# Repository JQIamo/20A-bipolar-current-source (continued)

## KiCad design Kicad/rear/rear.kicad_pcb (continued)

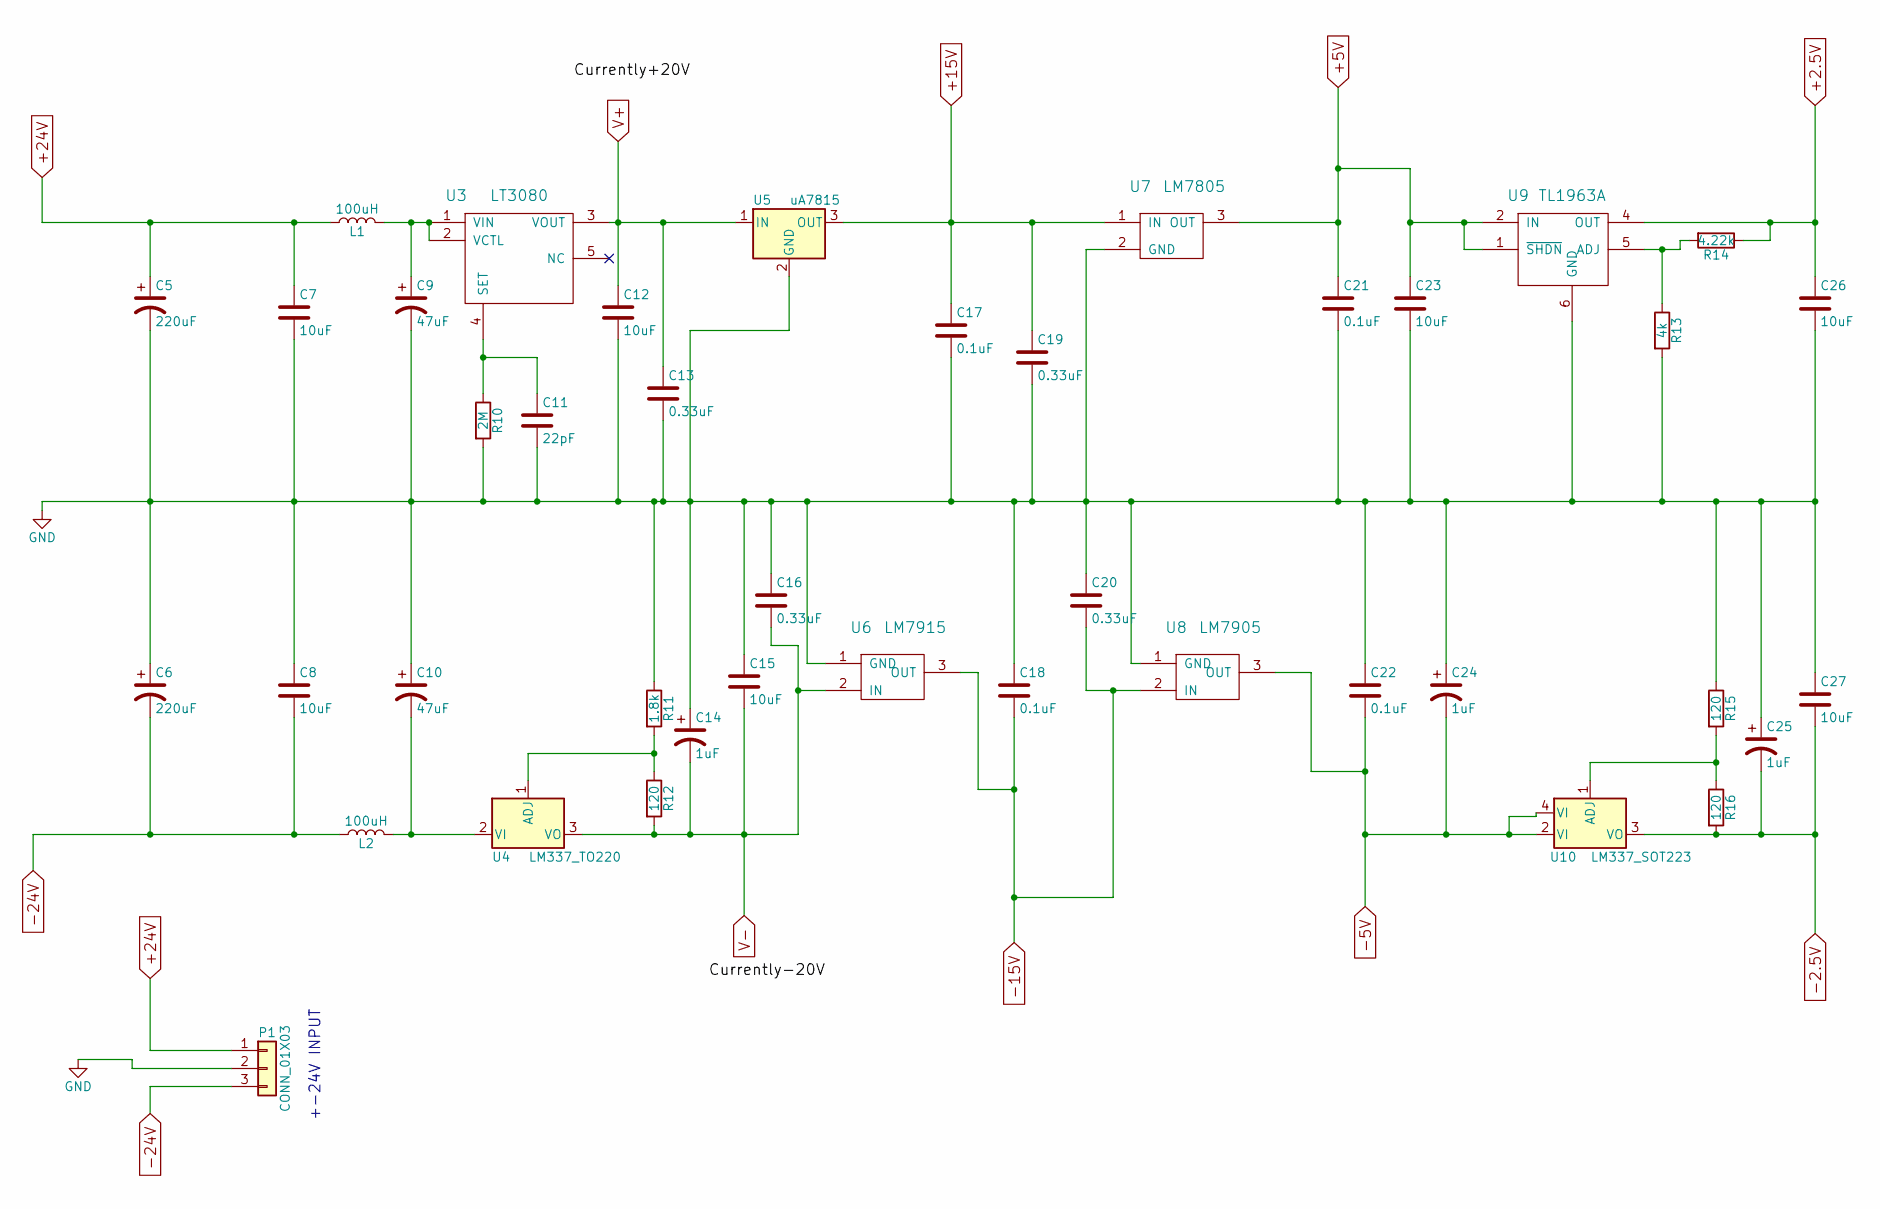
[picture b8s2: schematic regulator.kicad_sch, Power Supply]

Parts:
C5, C6: 220uF; CAP_polar_220uF; MPN EEE-1VA221UP; DIGIKEY PARTNO PCE3955CT-ND
C7, C8, C12, C15, C23, C26, C27: 10uF; C_1210; MPN C3225X7R1H106M250AC; DIGIKEY PARTNO 445-14933-1-ND
C9, C10: 47uF; CP_Tantalum_Case-X_EIA-7343-43_Reflow; MPN T495X476K035ATE300; DIGIKEY PARTNO 399-3905-1-ND
C11: 22pF; C_0402; MPN CL05C220JB5NNNC; DIGIKEY PARTNO 1276-1116-1-ND
C13, C16, C19, C20: 0.33uF; C_0603; MPN C1608X7R1H334K080AC; DIGIKEY PARTNO 445-5950-1-ND
C14, C24, C25: 1uF; CP_Tantalum_Case-B_EIA-3528-21_Reflow; MPN T491B105K050AT; DIGIKEY PARTNO 399-9720-1-ND
C17, C21, C22: 0.1uF; C_0603; MPN C0603C104J5RACAUTO; DIGIKEY PARTNO 399-6853-1-ND
C18: 0.1uF; C_0805; MPN C0603C104J5RACAUTO; DIGIKEY PARTNO 399-6853-1-ND
L1, L2: 100uH; Inductor_SLF10145; MPN SLF10145T-101M1R0-PF; DIGIKEY PARTNO 445-1976-1-ND
P1: CONN_01X03; Conn_01X03-3.5mm; MPN 1984620; DIGIKEY PARTNO 277-1722-ND
R10: 2M; R_0805; MPN ERJ-6ENF2004V; DIGIKEY PARTNO P2.00MCCT-ND
R11: 1.8k; R_0603; MPN PTN0603E1801BST1; DIGIKEY PARTNO 764-1393-1-ND
R12, R15, R16: 120; R_0603; MPN TNPW0603120RBEEA; DIGIKEY PARTNO 541-3165-1-ND
R13: 4k; R_0805; MPN CRCW08054K00FKTA; MOUSER PARTNO 71-CRCW0805-4K
R14: 4.22k; R_0603; MPN 6-2176088-6; DIGIKEY PARTNO A110168CT-ND
U3: LT3080; TO-220-5_Horizontal; MPN LT3080ET#PBF; DIGIKEY PARTNO LT3080ET#PBF-ND
U4: LM337_TO220; TO-220-3_Horizontal; MPN LM337KCSE3; DIGIKEY PARTNO 296-21577-5-ND
U5: uA7815; TO-220-3_Horizontal; MPN UA7815CKCS; DIGIKEY PARTNO 296-13999-5-ND
U6: LM7915; TO-220-3_Horizontal; MPN LM7915CT/NOPB; DIGIKEY PARTNO LM7915CT/NOPB-ND
U7: LM7805; TO-220-3_Horizontal; MPN LM7805CT/NOPB; DIGIKEY PARTNO 296-47192-ND
U8: LM7905; TO-220-3_Horizontal; MPN LM7905CT/NOPB; DIGIKEY PARTNO LM7905CTNS/NOPB-ND
U9: TL1963A; SOT-223-6; MPN TL1963ADCQR; DIGIKEY PARTNO 296-25119-1-ND
U10: LM337_SOT223; SOT-223; DIGIKEY PARTNO LM337IMPX/NOPBCT-ND

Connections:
+2.5V: C26.1, R14.1, U9.4 (OUT); also elsewhere on the board
+5V: C21.1, C23.1, U7.3 (OUT), U9.1 (~SHDN), U9.2 (IN); also elsewhere on the board
+15V: C17.1, C19.1, U5.3 (OUT), U7.1 (IN); also elsewhere on the board
+24V: C5.1, C7.1, L1.1, P1.1
-2.5V: C25.2, C27.2, R16.2, U10.3 (VO); also elsewhere on the board
-5V: C22.2, C24.2, U8.3 (OUT), U10.2 (VI), U10.4 (VI); also elsewhere on the board
-15V: C18.2, C20.2, U6.3 (OUT), U8.2 (IN); also elsewhere on the board
-24V: C6.2, C8.2, L2.1, P1.3
GND: C5.2, C6.1, C7.2, C8.1, C9.2, C10.1, C11.2, C12.2, C13.2, C14.1, C15.1, C16.1, C17.2, C18.1, C19.2, C20.1, C21.2, C22.1, C23.2, C24.1, C25.1, C26.2, C27.1, P1.2, R10.2, R11.1, R13.2, R15.1, U5.2 (GND), U6.1 (GND), U7.2 (GND), U8.1 (GND), U9.6 (GND); also elsewhere on the board
unnamed: C9.1, L1.2, U3.1 (VIN), U3.2 (VCTL)
unnamed: C10.2, L2.2, U4.2 (VI)
unnamed: C11.1, R10.1, U3.4 (SET)
unnamed: R11.2, R12.1, U4.1 (ADJ)
unnamed: R13.1, R14.2, U9.5 (ADJ)
unnamed: R15.2, R16.1, U10.1 (ADJ)
V+: C12.1, C13.1, U3.3 (VOUT), U5.1 (IN); also elsewhere on the board
V-: C14.2, C15.2, C16.2, R12.2, U4.3 (VO), U6.2 (IN); also elsewhere on the board

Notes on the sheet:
+-24V INPUT

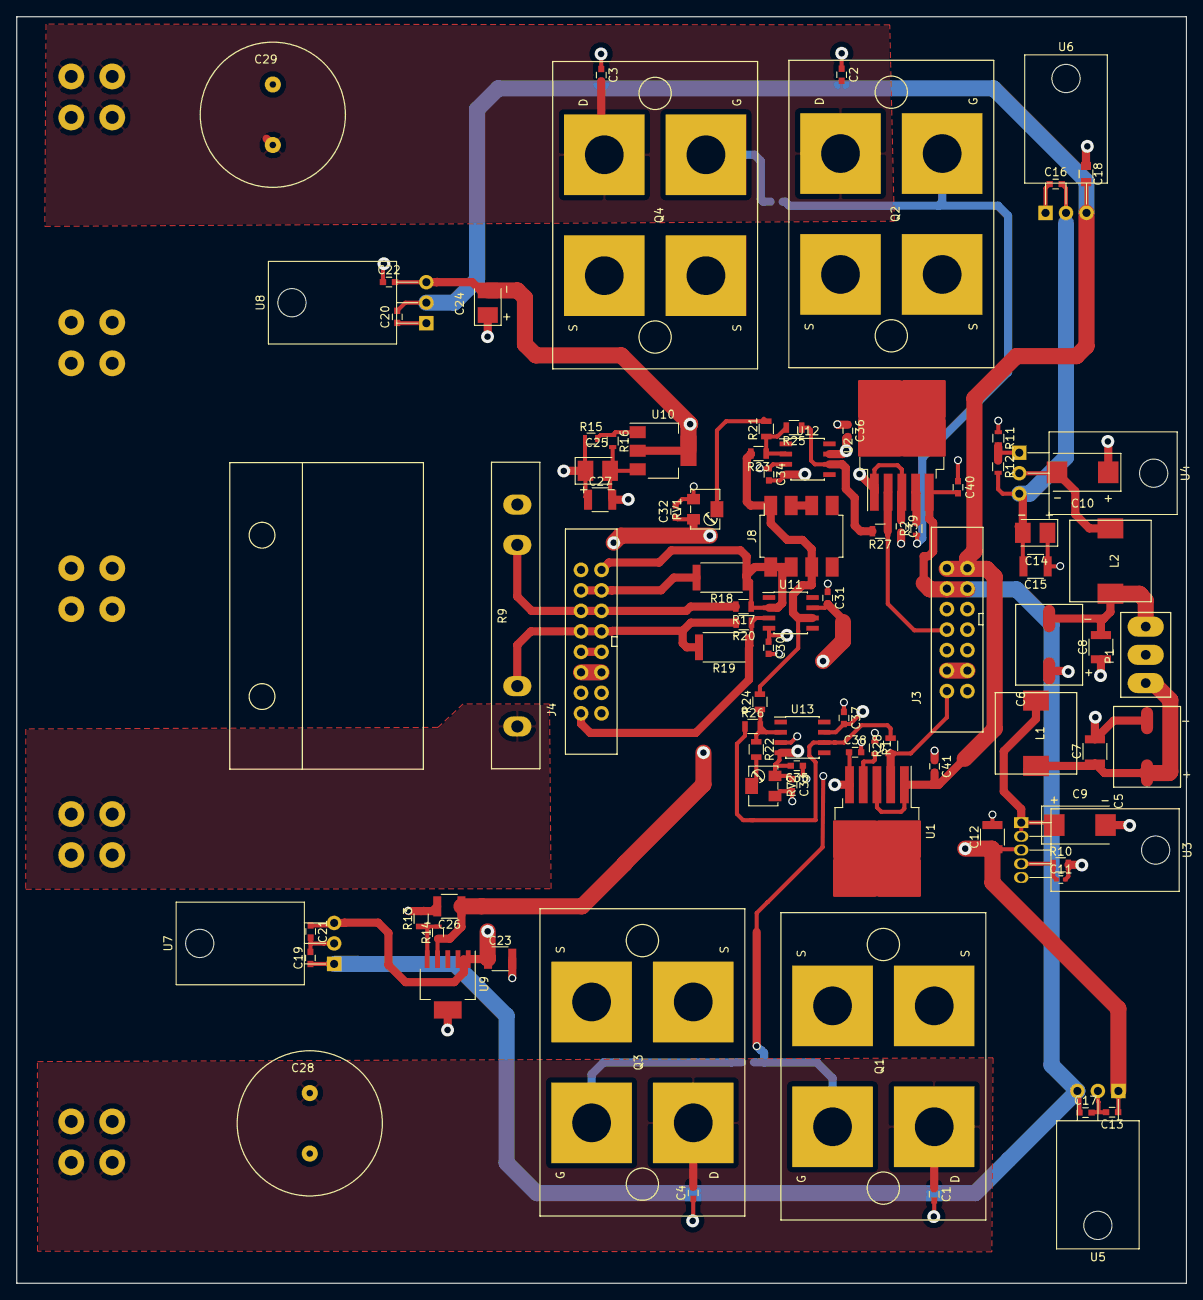
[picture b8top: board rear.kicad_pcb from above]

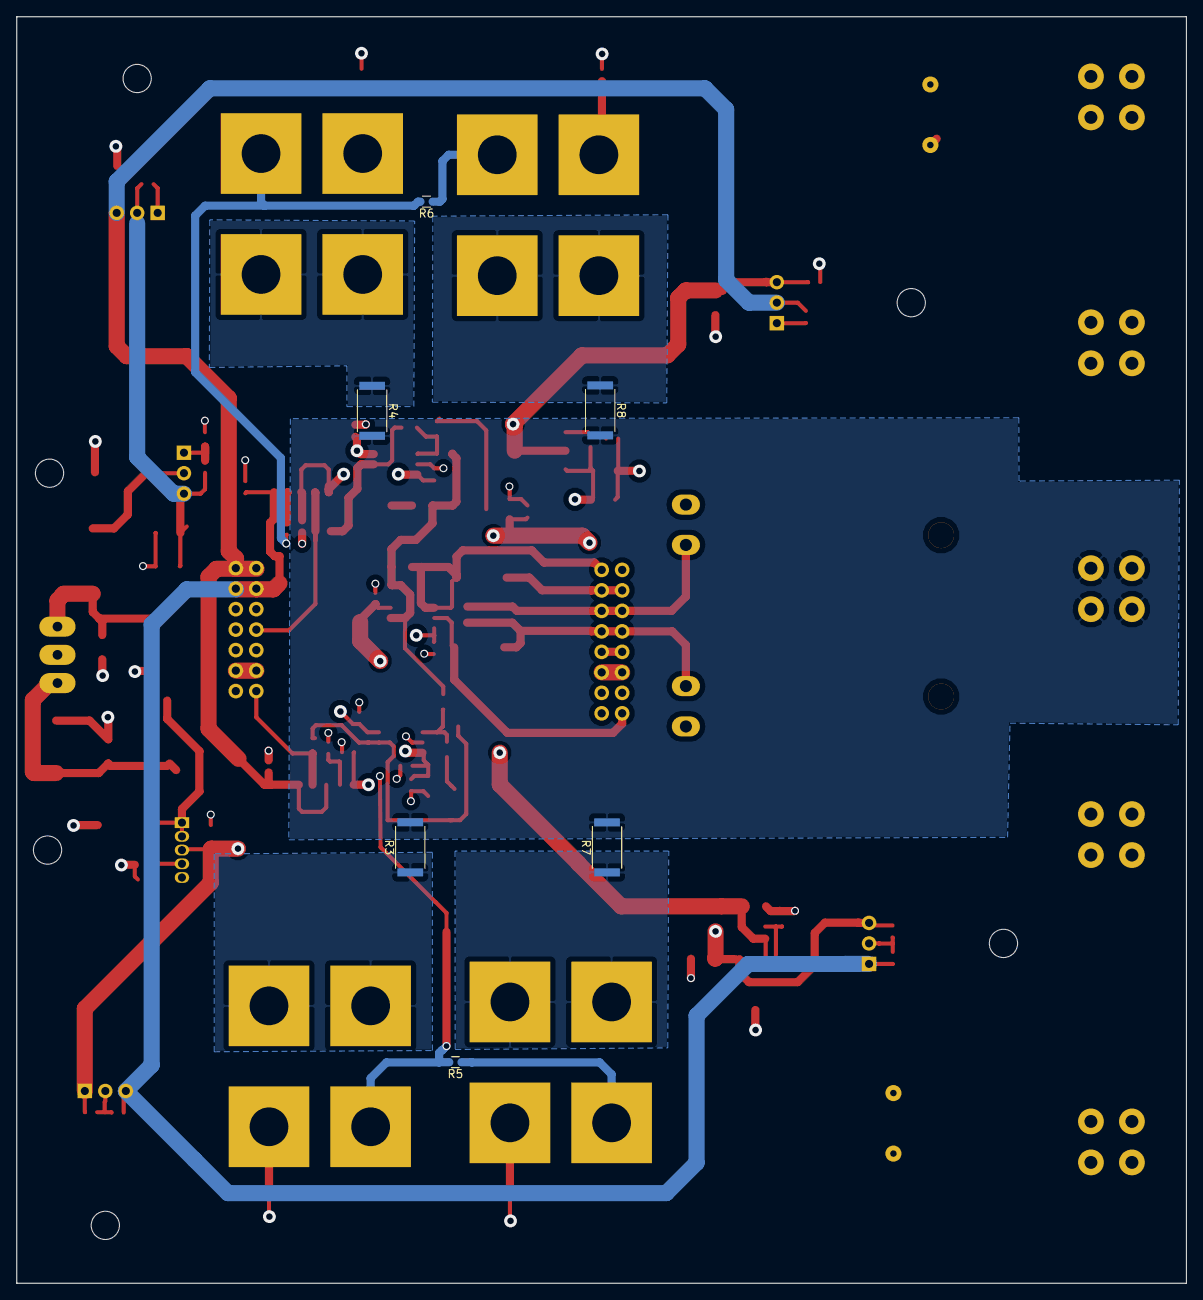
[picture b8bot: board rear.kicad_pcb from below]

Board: 4 copper layers, 145.0 x 157.0 mm, 99 parts (6 on the bottom side), 46 nets.

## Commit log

2023-05-15 Single Board Version
2025-05-27 Final Board schematics and layouts, Also added custom footprints that were made for the relay and terminal connector block.
2026-06-17 Irrelevant files removed
2026-06-17 Update README for project name and circuit details
2026-06-17 Removing garbage binaries
